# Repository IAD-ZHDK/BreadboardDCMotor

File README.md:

# Breadboard friendly DC motor pcb mount
This is as simple PCB for mounting cheap mini geared dc motors (from DSD Motor) to a breadboard. 

There are a number of variations of the motors, with either 3 or 6 volts and with various gear ratios. Joy-it offers the motor together with a wheel and mounting parts.

This is intended for teaching Physical Computing or electronic basics. When two breakouts are used together with the Joy-it wheel combo, it's possible to turn the breadboard into a differential wheeled robot. This project was born out of the frustration of leads always breaking on mini DC motors during Physical Computing classes.

To assemble, simply snap off the vertical bracket, and solder together with the motor into place. An optional drop of glue, or a 3D printed bracket (files included) can secure the motor firmly in place.  

PCB TOP                                                     |  PCB Bottom
:----------------------------------------------------------:|:---------------------------------------------------------------:
    |   
  	    	|  

## Parts
http://www.dsdmotor.com/product/DSD-12SSN20.pdf
https://joy-it.net/files/files/Produkte/COM-Motor03/COM-Motor03_Datasheet_2021-09-02.pdf

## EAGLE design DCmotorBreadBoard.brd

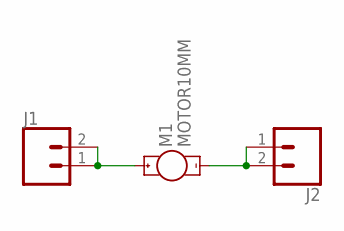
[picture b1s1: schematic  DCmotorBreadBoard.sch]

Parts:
J1, J2: CONN_02; 1X02
M1: MOTOR10MM; VIBE-MOTOR-10MM

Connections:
unnamed: J1.1, J1.2, M1.+
unnamed: J2.1, J2.2, M1.-

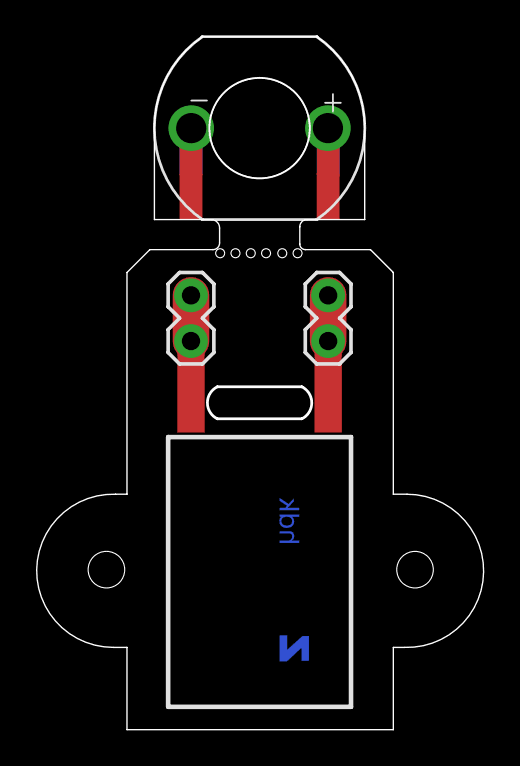
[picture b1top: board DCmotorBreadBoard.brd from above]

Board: 2 copper layers, 24.8 x 38.4 mm, 4 parts (1 on the bottom side), 2 nets.

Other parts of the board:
U$1: ZHDK_LOGO

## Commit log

2022-09-08 init commit
2022-09-08 fixed images
2022-09-08 added photo

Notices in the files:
parts and their libraries:
SparkFun-Connectors: Licensing: Creative Commons ShareAlike 4.0 International - https://creativecommons.org/licenses/by-sa/4.0
